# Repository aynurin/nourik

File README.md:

# NourK

ToDo:

 - [ ] Find a chip.
 - [#1](/../../issues/1) Create a layout
 - [#2](/../../issues/2) Find an existing PCB

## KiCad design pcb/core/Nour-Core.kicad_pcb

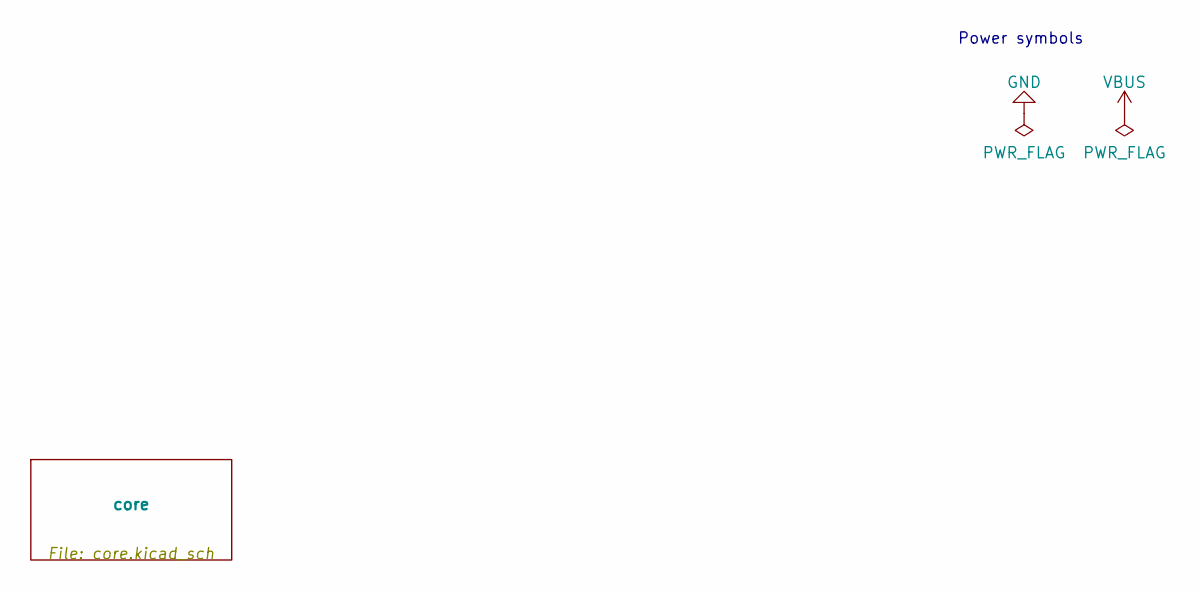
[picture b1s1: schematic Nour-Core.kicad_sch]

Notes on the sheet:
Power symbols

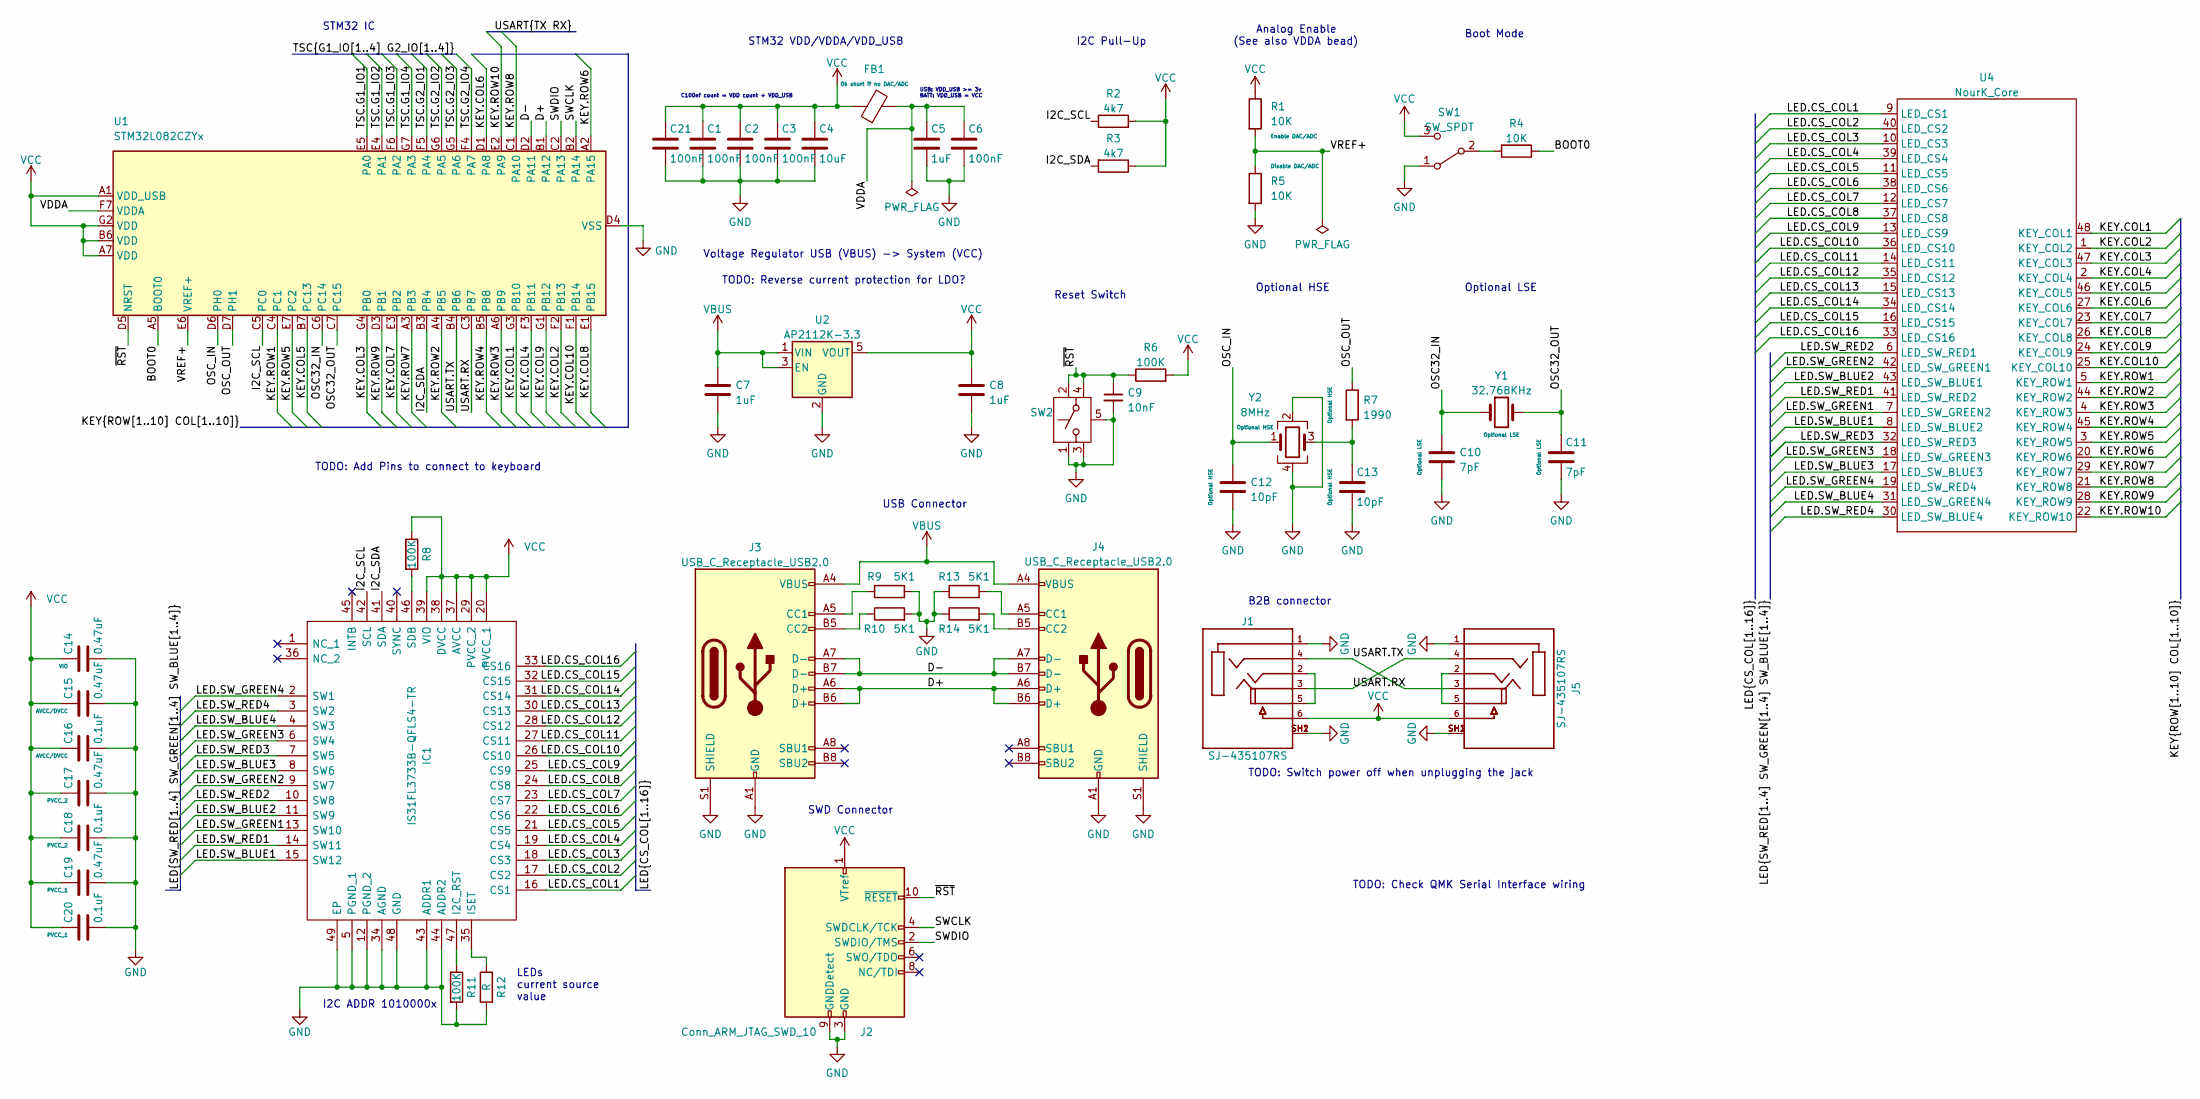
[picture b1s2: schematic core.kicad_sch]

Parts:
C1, C2, C3, C6, C21: 100nF; C_0805_2012Metric
C4: 10uF; C_0805_2012Metric
C5, C7, C8: 1uF; C_0805_2012Metric
C9: 10nF; C_0805_2012Metric
C10, C11: 7pF; C_0805_2012Metric
C12, C13: 10pF; C_0805_2012Metric
C14, C15, C17, C19: 0.47uF; C_0805_2012Metric
C16, C18, C20: 0.1uF; C_0805_2012Metric
FB1: FerriteBead; R_0805_2012Metric
IC1: IS31FL3733B-QFLS4-TR; QFN40P600X600X80-49N-D; Manufacturer_Part_Number IS31FL3733B-QFLS4-TR; Mouser Part Number 870-IS31FL3733BQFLS4
J1, J5: SJ-435107RS; CUI_SJ-435107RS
J2: Conn_ARM_JTAG_SWD_10; PinSocket_2x05_P1.27mm_Vertical
J3, J4: USB_C_Receptacle_USB2.0; GCT_USB4085-GF-A_REVA4
R1, R4, R5: 10K; R_0805_2012Metric
R2, R3: 4k7; R_0805_2012Metric
R6, R8, R11: 100K; R_0805_2012Metric
R7: 1990; R_0805_2012Metric
R9, R10, R13, R14: 5K1; R_0805_2012Metric
R12: R; R_0805_2012Metric
SW1: SW_SPDT; CSS-1211TB
SW2: SW_SPST_G; EVQP9102W; PartNo EVQ-P9102W
U1: STM32L082CZYx; ST_WLCSP-49_Die447
U2: AP2112K-3.3; SOT-23-5
U4: NourK_Core; Nour_Core
Y1: 32.768KHz; ECS327712TR; PartNo ECS-.327-7-12-TR
Y2: 8MHz; ECS801830BAGNTR; PartNo ECS-80-10-30B-CWN-TR

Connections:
/core/BOOT0: R4.1, U1.A5 (BOOT0)
/core/D+: J3.A6 (D+), J3.B6 (D+), J4.A6 (D+), J4.B6 (D+), U1.B1 (PA12)
/core/D-: J3.A7 (D-), J3.B7 (D-), J4.A7 (D-), J4.B7 (D-), U1.D2 (PA11)
/core/I2C_SCL: IC1.42 (SCL), R2.1, U1.C5 (PC0)
/core/I2C_SDA: IC1.41 (SDA), R3.2, U1.B3 (PB4)
/core/KEY.COL1: U1.G3 (PB10), U4.48 (KEY_COL1)
/core/KEY.COL2: U1.F2 (PB13), U4.1 (KEY_COL2)
/core/KEY.COL3: U1.G4 (PB0), U4.47 (KEY_COL3)
/core/KEY.COL4: U1.F3 (PB11), U4.2 (KEY_COL4)
/core/KEY.COL5: U1.B7 (PC13), U4.46 (KEY_COL5)
/core/KEY.COL6: U1.D1 (PA8), U4.27 (KEY_COL6)
/core/KEY.COL7: U1.E3 (PB2), U4.23 (KEY_COL7)
/core/KEY.COL8: U1.E1 (PB15), U4.26 (KEY_COL8)
/core/KEY.COL9: U1.G1 (PB12), U4.24 (KEY_COL9)
/core/KEY.COL10: U1.F1 (PB14), U4.25 (KEY_COL10)
/core/KEY.ROW1: U1.C4 (PC1), U4.5 (KEY_ROW1)
/core/KEY.ROW2: U1.A4 (PB5), U4.44 (KEY_ROW2)
/core/KEY.ROW3: U1.A6 (PB9), U4.4 (KEY_ROW3)
/core/KEY.ROW4: U1.B5 (PB8), U4.45 (KEY_ROW4)
/core/KEY.ROW5: U1.E7 (PC2), U4.3 (KEY_ROW5)
/core/KEY.ROW6: U1.A2 (PA15), U4.20 (KEY_ROW6)
/core/KEY.ROW7: U1.A3 (PB3), U4.29 (KEY_ROW7)
/core/KEY.ROW8: U1.C1 (PA10), U4.21 (KEY_ROW8)
/core/KEY.ROW9: U1.D3 (PB1), U4.28 (KEY_ROW9)
/core/KEY.ROW10: U1.E2 (PA9), U4.22 (KEY_ROW10)
/core/LED.CS_COL1: IC1.16 (CS1), U4.9 (LED_CS1)
/core/LED.CS_COL2: IC1.17 (CS2), U4.40 (LED_CS2)
/core/LED.CS_COL3: IC1.18 (CS3), U4.10 (LED_CS3)
/core/LED.CS_COL4: IC1.19 (CS4), U4.39 (LED_CS4)
/core/LED.CS_COL5: IC1.21 (CS5), U4.11 (LED_CS5)
/core/LED.CS_COL6: IC1.22 (CS6), U4.38 (LED_CS6)
/core/LED.CS_COL7: IC1.23 (CS7), U4.12 (LED_CS7)
/core/LED.CS_COL8: IC1.24 (CS8), U4.37 (LED_CS8)
/core/LED.CS_COL9: IC1.25 (CS9), U4.13 (LED_CS9)
/core/LED.CS_COL10: IC1.26 (CS10), U4.36 (LED_CS10)
/core/LED.CS_COL11: IC1.27 (CS11), U4.14 (LED_CS11)
/core/LED.CS_COL12: IC1.28 (CS12), U4.35 (LED_CS12)
/core/LED.CS_COL13: IC1.30 (CS13), U4.15 (LED_CS13)
/core/LED.CS_COL14: IC1.31 (CS14), U4.34 (LED_CS14)
/core/LED.CS_COL15: IC1.32 (CS15), U4.16 (LED_CS15)
/core/LED.CS_COL16: IC1.33 (CS16), U4.33 (LED_CS16)
/core/LED.SW_BLUE1: IC1.15 (SW12), U4.8 (LED_SW_BLUE2)
/core/LED.SW_BLUE2: IC1.11 (SW9), U4.43 (LED_SW_BLUE1)
/core/LED.SW_BLUE3: IC1.8 (SW6), U4.17 (LED_SW_BLUE3)
/core/LED.SW_BLUE4: IC1.4 (SW3), U4.31 (LED_SW_GREEN4)
/core/LED.SW_GREEN1: IC1.13 (SW10), U4.7 (LED_SW_GREEN2)
/core/LED.SW_GREEN2: IC1.9 (SW7), U4.42 (LED_SW_GREEN1)
/core/LED.SW_GREEN3: IC1.6 (SW4), U4.18 (LED_SW_GREEN3)
/core/LED.SW_GREEN4: IC1.2 (SW1), U4.19 (LED_SW_RED4)
/core/LED.SW_RED1: IC1.14 (SW11), U4.41 (LED_SW_RED2)
/core/LED.SW_RED2: IC1.10 (SW8), U4.6 (LED_SW_RED1)
/core/LED.SW_RED3: IC1.7 (SW5), U4.32 (LED_SW_RED3)
/core/LED.SW_RED4: IC1.3 (SW2), U4.30 (LED_SW_BLUE4)
/core/OSC32_IN: C10.1, U1.C6 (PC14), Y1.1
/core/OSC32_OUT: C11.1, U1.C7 (PC15), Y1.2
/core/OSC_IN: C12.1, U1.D6 (PH0), Y2.1
/core/OSC_OUT: R7.1, U1.D7 (PH1)
/core/SWCLK: J2.4 (SWDCLK/TCK), U1.B2 (PA14)
/core/SWDIO: J2.2 (SWDIO/TMS), U1.C2 (PA13)
/core/TSC.G1_IO1: U1.E5 (PA0)
/core/TSC.G1_IO2: U1.E4 (PA1)
/core/TSC.G1_IO3: U1.F6 (PA2)
/core/TSC.G1_IO4: U1.G7 (PA3)
/core/TSC.G2_IO1: U1.F5 (PA4)
/core/TSC.G2_IO2: U1.G6 (PA5)
/core/TSC.G2_IO3: U1.G5 (PA6)
/core/TSC.G2_IO4: U1.F4 (PA7)
/core/USART.RX: J1.3, J5.4, U1.C3 (PB7)
/core/USART.TX: J1.4, J5.3, U1.B4 (PB6)
/core/VDDA: C5.1, C6.1, FB1.2, U1.F7 (VDDA)
/core/VREF+: R1.2, R5.1, U1.E6 (VREF+)
/core/~RST: C9.1, J2.10 (~RESET), R6.1, SW2.2 (B), SW2.4 (B), U1.D5 (NRST)
GND: C1.2, C2.2, C3.2, C4.2, C5.2, C6.2, C7.2, C8.2, C9.2, C10.2, C11.2, C12.2, C13.2, C14.2, C15.2, C16.2, C17.2, C18.2, C19.2, C20.2, C21.2, IC1.5 (PGND_1), IC1.12 (PGND_2), IC1.34 (AGND), IC1.43 (ADDR1), IC1.44 (ADDR2), IC1.48 (GND), IC1.49 (EP), J1.1, J1.SH1, J1.SH2, J2.3 (GND), J2.5 (GND), J2.9 (GNDDetect), J3.A1 (GND), J3.A12 (GND), J3.B1 (GND), J3.B12 (GND), J3.S1 (SHIELD), J4.A1 (GND), J4.A12 (GND), J4.B1 (GND), J4.B12 (GND), J4.S1 (SHIELD), J5.1, J5.SH1, J5.SH2, R5.2, R9.2, R10.2, R11.2, R12.2, R13.1, R14.1, SW1.1 (A), SW2.1 (A), SW2.3 (A), SW2.5 (G), U1.D4 (VSS), U2.2 (GND), Y2.2, Y2.4
unnamed: C13.1, R7.2, Y2.3
unnamed: IC1.35 (ISET), R12.1
unnamed: IC1.46 (SDB), R8.2
unnamed: IC1.47 (I2C_RST), R11.1
unnamed: J1.2, J1.5
unnamed: J3.A5 (CC1), R9.1
unnamed: J3.B5 (CC2), R10.1
unnamed: J4.A5 (CC1), R13.2
unnamed: J4.B5 (CC2), R14.2
unnamed: J5.2, J5.5
unnamed: R4.2, SW1.2 (B)
VBUS: C7.1, J3.A4 (VBUS), J3.A9 (VBUS), J3.B4 (VBUS), J3.B9 (VBUS), J4.A4 (VBUS), J4.A9 (VBUS), J4.B4 (VBUS), J4.B9 (VBUS), U2.1 (VIN), U2.3 (EN)
VCC: C1.1, C2.1, C3.1, C4.1, C8.1, C14.1, C15.1, C16.1, C17.1, C18.1, C19.1, C20.1, C21.1, FB1.1, IC1.20 (PVCC_1), IC1.29 (PVCC_2), IC1.37 (AVCC), IC1.38 (DVCC), IC1.39 (VIO), J1.6, J2.1 (VTref), J5.6, R1.1, R2.2, R3.1, R6.2, R8.1, SW1.3 (C), U1.A1 (VDD_USB), U1.A7 (VDD), U1.B6 (VDD), U1.G2 (VDD), U2.5 (VOUT)

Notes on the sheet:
Boot Mode
Voltage Regulator USB (VBUS) -> System (VCC)
C100nf count = VDD count + VDD_USB
STM32 VDD/VDDA/VDD_USB
I2C Pull-Up
Optional LSE
LEDs current source value
TODO: Switch power off when unplugging the jack
I2C ADDR 1010000x
Optional HSE
Reset Switch
STM32 IC
TODO: Check QMK Serial Interface wiring
Analog Enable (See also VDDA bead)
SWD Connector
TODO: Reverse current protection for LDO?
USB Connector
TODO: Add Pins to connect to keyboard
B2B connector
USB: VDD_USB >= 3v BATT: VDD_USB = VCC

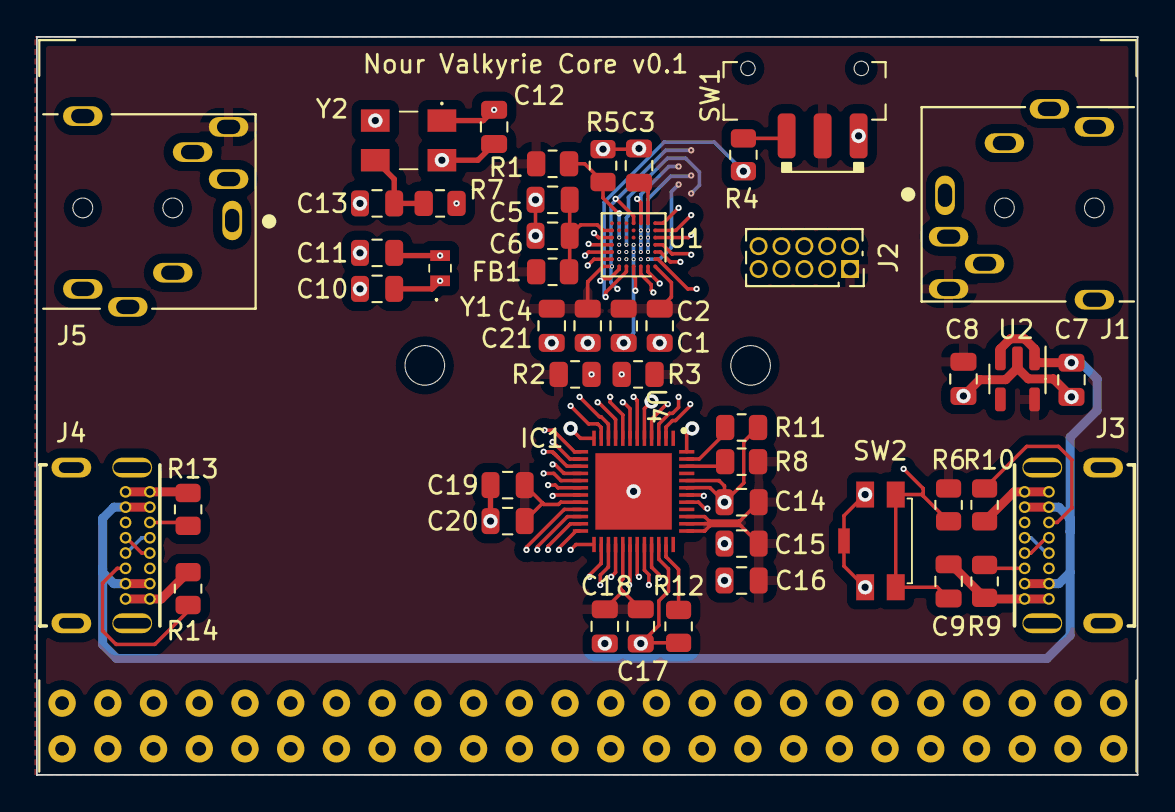
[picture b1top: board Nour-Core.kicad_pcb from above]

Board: 4 copper layers, 61.2 x 41.0 mm, 49 parts (0 on the bottom side), 78 nets.

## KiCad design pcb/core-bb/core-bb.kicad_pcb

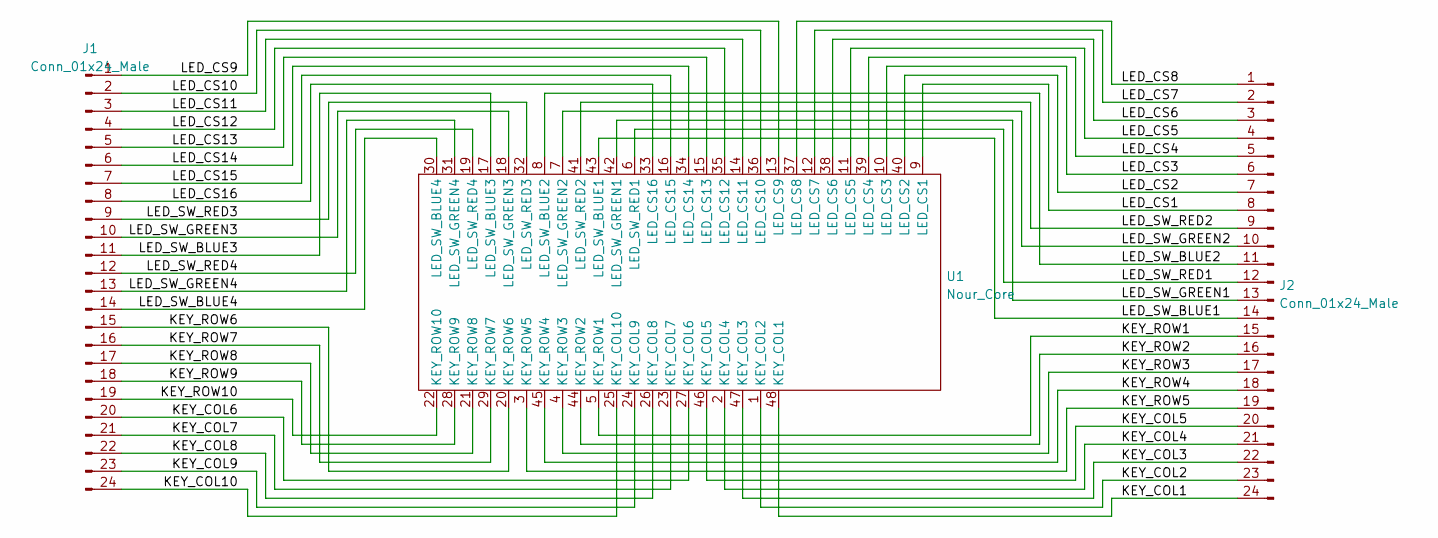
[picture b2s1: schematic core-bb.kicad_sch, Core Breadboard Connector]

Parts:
J1, J2: Conn_01x24_Male; PinHeader_1x24_P2.54mm_Vertical
U1: Nour_Core

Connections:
/KEY_COL1: J2.24, U1.48 (KEY_COL1)
/KEY_COL2: J2.23, U1.1 (KEY_COL2)
/KEY_COL3: J2.22, U1.47 (KEY_COL3)
/KEY_COL4: J2.21, U1.2 (KEY_COL4)
/KEY_COL5: J2.20, U1.46 (KEY_COL5)
/KEY_COL6: J1.20, U1.27 (KEY_COL6)
/KEY_COL7: J1.21, U1.23 (KEY_COL7)
/KEY_COL8: J1.22, U1.26 (KEY_COL8)
/KEY_COL9: J1.23, U1.24 (KEY_COL9)
/KEY_COL10: J1.24, U1.25 (KEY_COL10)
/KEY_ROW1: J2.15, U1.5 (KEY_ROW1)
/KEY_ROW2: J2.16, U1.44 (KEY_ROW2)
/KEY_ROW3: J2.17, U1.4 (KEY_ROW3)
/KEY_ROW4: J2.18, U1.45 (KEY_ROW4)
/KEY_ROW5: J2.19, U1.3 (KEY_ROW5)
/KEY_ROW6: J1.15, U1.20 (KEY_ROW6)
/KEY_ROW7: J1.16, U1.29 (KEY_ROW7)
/KEY_ROW8: J1.17, U1.21 (KEY_ROW8)
/KEY_ROW9: J1.18, U1.28 (KEY_ROW9)
/KEY_ROW10: J1.19, U1.22 (KEY_ROW10)
/LED_CS1: J2.8, U1.9 (LED_CS1)
/LED_CS2: J2.7, U1.40 (LED_CS2)
/LED_CS3: J2.6, U1.10 (LED_CS3)
/LED_CS4: J2.5, U1.39 (LED_CS4)
/LED_CS5: J2.4, U1.11 (LED_CS5)
/LED_CS6: J2.3, U1.38 (LED_CS6)
/LED_CS7: J2.2, U1.12 (LED_CS7)
/LED_CS8: J2.1, U1.37 (LED_CS8)
/LED_CS9: J1.1, U1.13 (LED_CS9)
/LED_CS10: J1.2, U1.36 (LED_CS10)
/LED_CS11: J1.3, U1.14 (LED_CS11)
/LED_CS12: J1.4, U1.35 (LED_CS12)
/LED_CS13: J1.5, U1.15 (LED_CS13)
/LED_CS14: J1.6, U1.34 (LED_CS14)
/LED_CS15: J1.7, U1.16 (LED_CS15)
/LED_CS16: J1.8, U1.33 (LED_CS16)
/LED_SW_BLUE1: J2.14, U1.43 (LED_SW_BLUE1)
/LED_SW_BLUE2: J2.11, U1.8 (LED_SW_BLUE2)
/LED_SW_BLUE3: J1.11, U1.17 (LED_SW_BLUE3)
/LED_SW_BLUE4: J1.14, U1.30 (LED_SW_BLUE4)
/LED_SW_GREEN1: J2.13, U1.42 (LED_SW_GREEN1)
/LED_SW_GREEN2: J2.10, U1.7 (LED_SW_GREEN2)
/LED_SW_GREEN3: J1.10, U1.18 (LED_SW_GREEN3)
/LED_SW_GREEN4: J1.13, U1.31 (LED_SW_GREEN4)
/LED_SW_RED1: J2.12, U1.6 (LED_SW_RED1)
/LED_SW_RED2: J2.9, U1.41 (LED_SW_RED2)
/LED_SW_RED3: J1.9, U1.32 (LED_SW_RED3)
/LED_SW_RED4: J1.12, U1.19 (LED_SW_RED4)

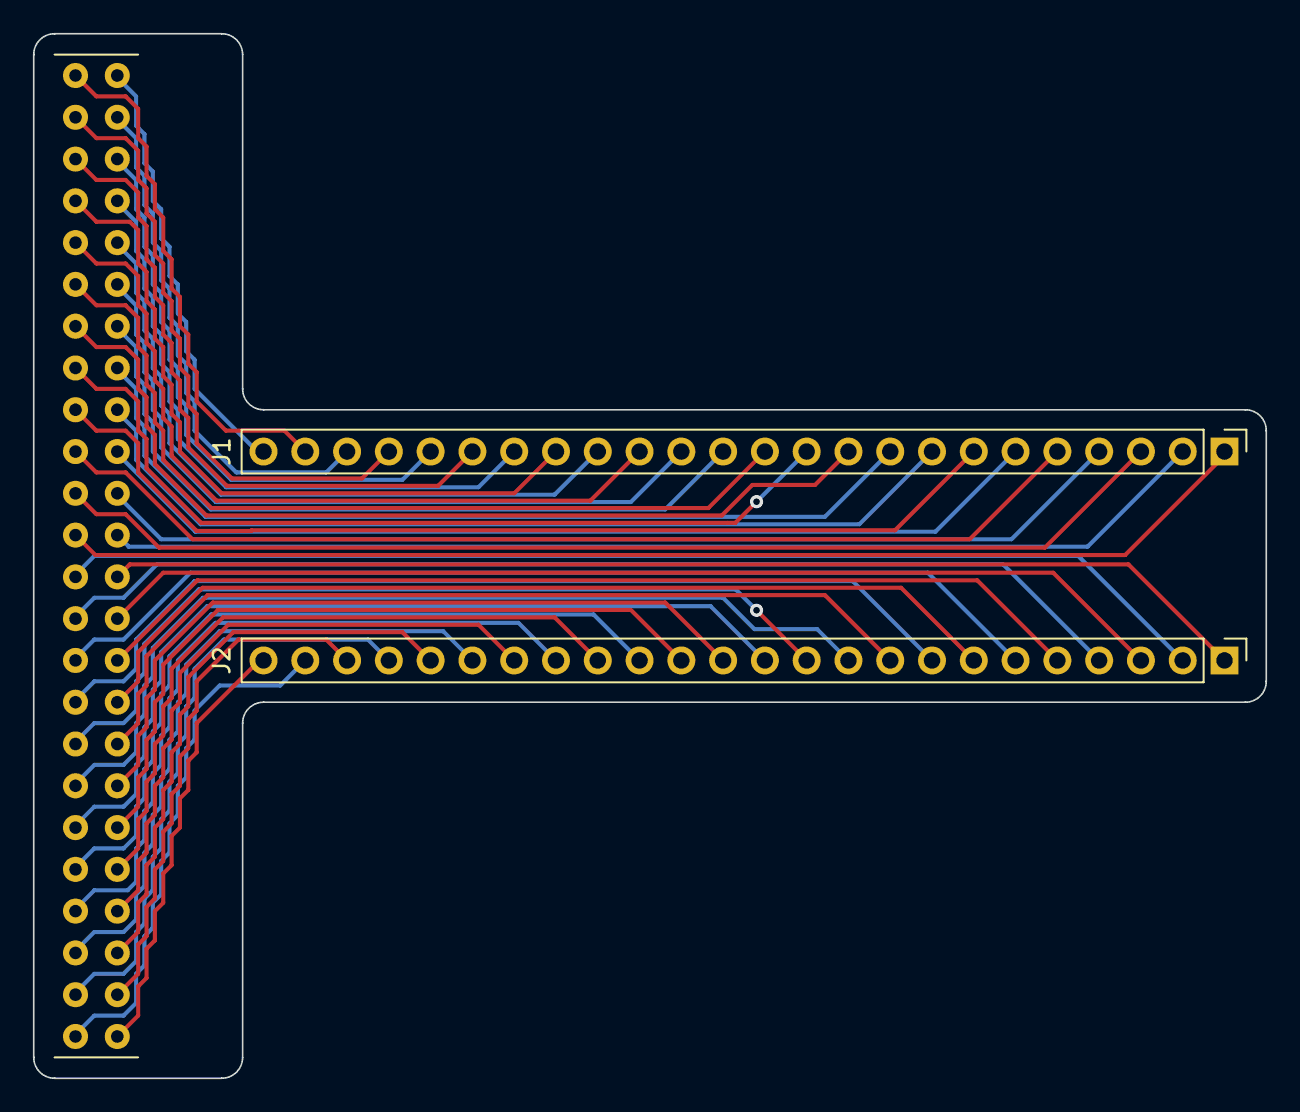
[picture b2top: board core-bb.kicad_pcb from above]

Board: 2 copper layers, 74.9 x 63.5 mm, 3 parts (0 on the bottom side), 48 nets.

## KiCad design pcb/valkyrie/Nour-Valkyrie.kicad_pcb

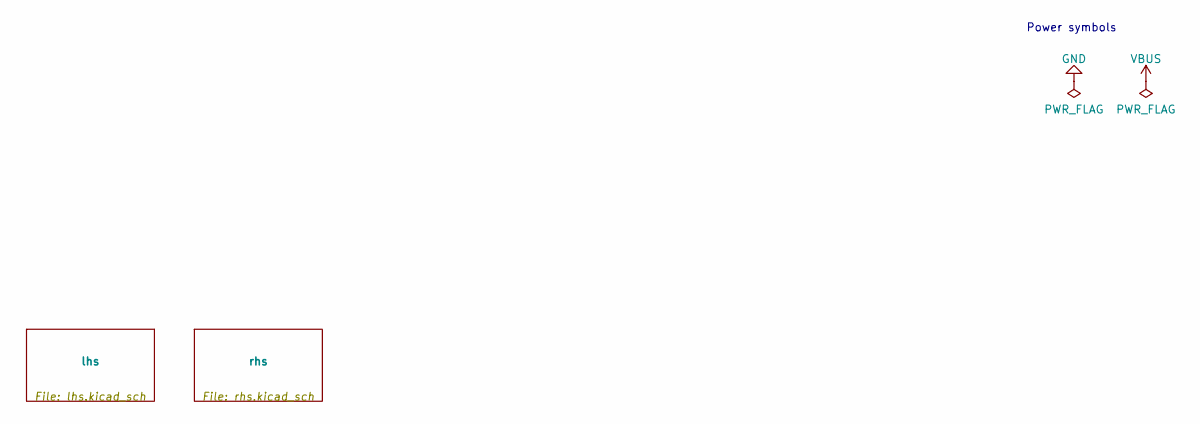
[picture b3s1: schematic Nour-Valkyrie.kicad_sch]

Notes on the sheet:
Power symbols

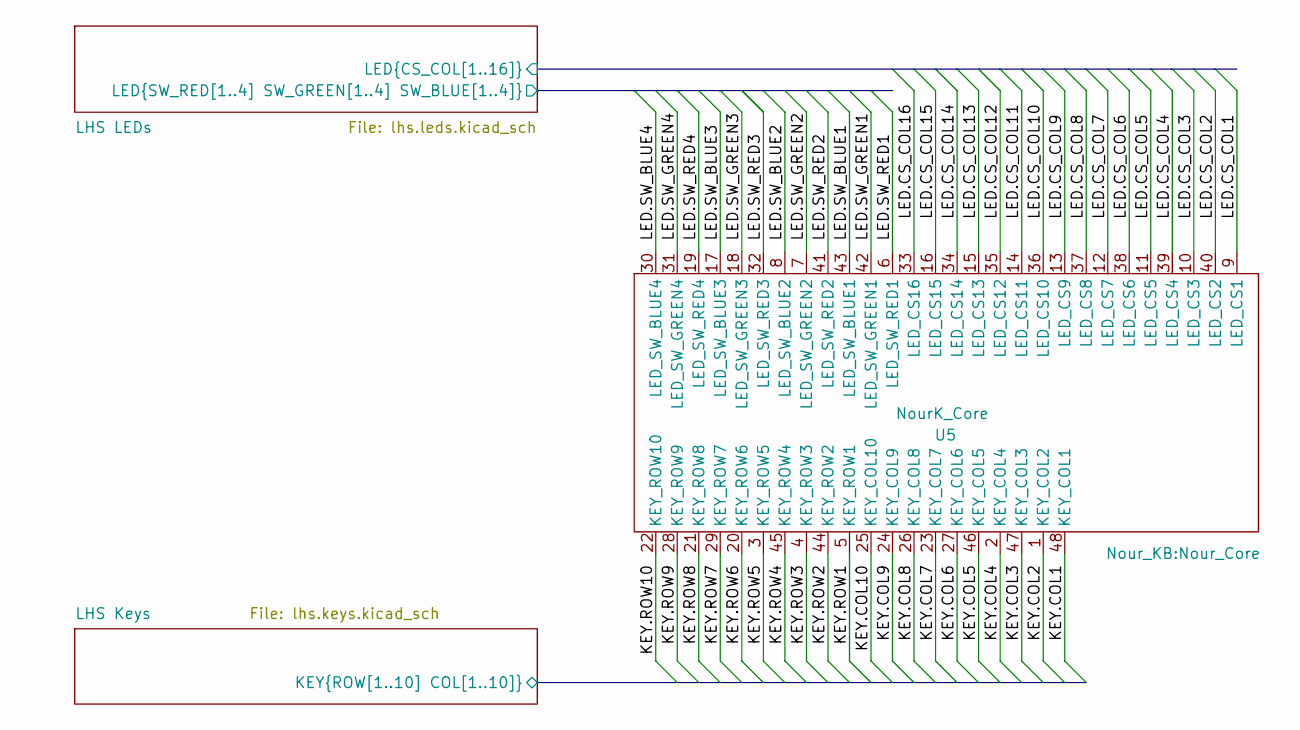
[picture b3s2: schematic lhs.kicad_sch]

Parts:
U5: NourK_Core; Nour_Core

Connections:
/lhs/LHS Keys/KEY.COL1: U5.48 (KEY_COL1); also elsewhere on the board
/lhs/LHS Keys/KEY.COL2: U5.1 (KEY_COL2); also elsewhere on the board
/lhs/LHS Keys/KEY.COL3: U5.47 (KEY_COL3); also elsewhere on the board
/lhs/LHS Keys/KEY.COL4: U5.2 (KEY_COL4); also elsewhere on the board
/lhs/LHS Keys/KEY.COL5: U5.46 (KEY_COL5); also elsewhere on the board
/lhs/LHS Keys/KEY.COL6: U5.27 (KEY_COL6); also elsewhere on the board
/lhs/LHS Keys/KEY.COL7: U5.23 (KEY_COL7); also elsewhere on the board
/lhs/LHS Keys/KEY.COL8: U5.26 (KEY_COL8)
/lhs/LHS Keys/KEY.COL9: U5.24 (KEY_COL9)
/lhs/LHS Keys/KEY.COL10: U5.25 (KEY_COL10)
/lhs/LHS Keys/KEY.ROW1: U5.5 (KEY_ROW1); also elsewhere on the board
/lhs/LHS Keys/KEY.ROW2: U5.44 (KEY_ROW2); also elsewhere on the board
/lhs/LHS Keys/KEY.ROW3: U5.4 (KEY_ROW3)
/lhs/LHS Keys/KEY.ROW4: U5.45 (KEY_ROW4)
/lhs/LHS Keys/KEY.ROW5: U5.3 (KEY_ROW5)
/lhs/LHS Keys/KEY.ROW6: U5.20 (KEY_ROW6)
/lhs/LHS Keys/KEY.ROW7: U5.29 (KEY_ROW7)
/lhs/LHS Keys/KEY.ROW8: U5.21 (KEY_ROW8)
/lhs/LHS Keys/KEY.ROW9: U5.28 (KEY_ROW9); also elsewhere on the board
/lhs/LHS Keys/KEY.ROW10: U5.22 (KEY_ROW10); also elsewhere on the board
/lhs/LHS LEDs/LED.CS_COL1: U5.9 (LED_CS1); also elsewhere on the board
/lhs/LHS LEDs/LED.CS_COL2: U5.40 (LED_CS2); also elsewhere on the board
/lhs/LHS LEDs/LED.CS_COL3: U5.10 (LED_CS3); also elsewhere on the board
/lhs/LHS LEDs/LED.CS_COL4: U5.39 (LED_CS4); also elsewhere on the board
/lhs/LHS LEDs/LED.CS_COL5: U5.11 (LED_CS5); also elsewhere on the board
/lhs/LHS LEDs/LED.CS_COL6: U5.38 (LED_CS6); also elsewhere on the board
/lhs/LHS LEDs/LED.CS_COL7: U5.12 (LED_CS7); also elsewhere on the board
/lhs/LHS LEDs/LED.CS_COL8: U5.37 (LED_CS8); also elsewhere on the board
/lhs/LHS LEDs/LED.CS_COL9: U5.13 (LED_CS9); also elsewhere on the board
/lhs/LHS LEDs/LED.CS_COL10: U5.36 (LED_CS10); also elsewhere on the board
/lhs/LHS LEDs/LED.CS_COL11: U5.14 (LED_CS11); also elsewhere on the board
/lhs/LHS LEDs/LED.CS_COL12: U5.35 (LED_CS12)
/lhs/LHS LEDs/LED.CS_COL13: U5.15 (LED_CS13)
/lhs/LHS LEDs/LED.CS_COL14: U5.34 (LED_CS14)
/lhs/LHS LEDs/LED.CS_COL15: U5.16 (LED_CS15)
/lhs/LHS LEDs/LED.CS_COL16: U5.33 (LED_CS16)
/lhs/LHS LEDs/LED.SW_BLUE1: U5.43 (LED_SW_BLUE1); also elsewhere on the board
/lhs/LHS LEDs/LED.SW_BLUE2: U5.8 (LED_SW_BLUE2); also elsewhere on the board
/lhs/LHS LEDs/LED.SW_BLUE3: U5.17 (LED_SW_BLUE3); also elsewhere on the board
/lhs/LHS LEDs/LED.SW_BLUE4: U5.30 (LED_SW_BLUE4); also elsewhere on the board
/lhs/LHS LEDs/LED.SW_GREEN1: U5.42 (LED_SW_GREEN1); also elsewhere on the board
/lhs/LHS LEDs/LED.SW_GREEN2: U5.7 (LED_SW_GREEN2); also elsewhere on the board
/lhs/LHS LEDs/LED.SW_GREEN3: U5.18 (LED_SW_GREEN3); also elsewhere on the board
/lhs/LHS LEDs/LED.SW_GREEN4: U5.31 (LED_SW_GREEN4); also elsewhere on the board
/lhs/LHS LEDs/LED.SW_RED1: U5.6 (LED_SW_RED1); also elsewhere on the board
/lhs/LHS LEDs/LED.SW_RED2: U5.41 (LED_SW_RED2); also elsewhere on the board
/lhs/LHS LEDs/LED.SW_RED3: U5.32 (LED_SW_RED3); also elsewhere on the board
/lhs/LHS LEDs/LED.SW_RED4: U5.19 (LED_SW_RED4); also elsewhere on the board

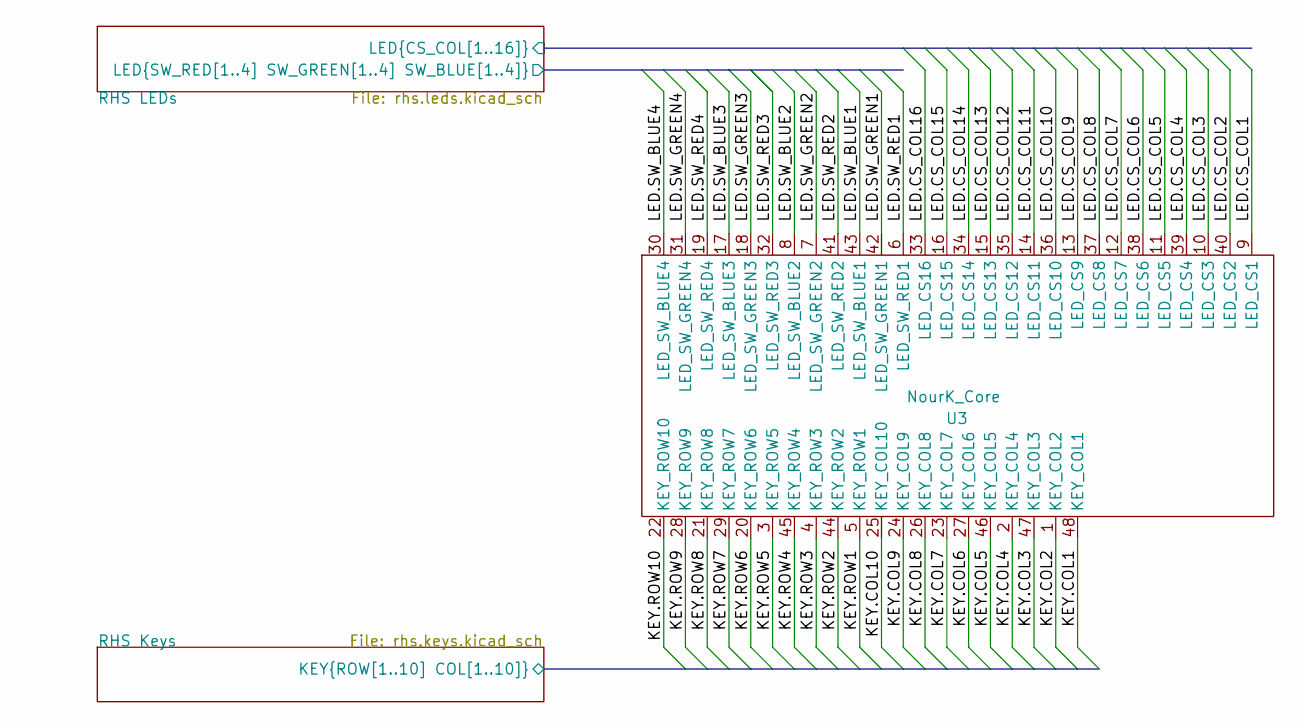
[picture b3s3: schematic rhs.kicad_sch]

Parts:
U3: NourK_Core; Nour_Core

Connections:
/rhs/RHS Keys/KEY.COL1: U3.48 (KEY_COL1); also elsewhere on the board
/rhs/RHS Keys/KEY.COL2: U3.1 (KEY_COL2); also elsewhere on the board
/rhs/RHS Keys/KEY.COL3: U3.47 (KEY_COL3)
/rhs/RHS Keys/KEY.COL4: U3.2 (KEY_COL4)
/rhs/RHS Keys/KEY.COL5: U3.46 (KEY_COL5)
/rhs/RHS Keys/KEY.COL6: U3.27 (KEY_COL6); also elsewhere on the board
/rhs/RHS Keys/KEY.COL7: U3.23 (KEY_COL7); also elsewhere on the board
/rhs/RHS Keys/KEY.COL8: U3.26 (KEY_COL8); also elsewhere on the board
/rhs/RHS Keys/KEY.COL9: U3.24 (KEY_COL9); also elsewhere on the board
/rhs/RHS Keys/KEY.COL10: U3.25 (KEY_COL10); also elsewhere on the board
/rhs/RHS Keys/KEY.ROW1: U3.5 (KEY_ROW1)
/rhs/RHS Keys/KEY.ROW2: U3.44 (KEY_ROW2)
/rhs/RHS Keys/KEY.ROW3: U3.4 (KEY_ROW3); also elsewhere on the board
/rhs/RHS Keys/KEY.ROW4: U3.45 (KEY_ROW4); also elsewhere on the board
/rhs/RHS Keys/KEY.ROW5: U3.3 (KEY_ROW5)
/rhs/RHS Keys/KEY.ROW6: U3.20 (KEY_ROW6)
/rhs/RHS Keys/KEY.ROW7: U3.29 (KEY_ROW7)
/rhs/RHS Keys/KEY.ROW8: U3.21 (KEY_ROW8); also elsewhere on the board
/rhs/RHS Keys/KEY.ROW9: U3.28 (KEY_ROW9); also elsewhere on the board
/rhs/RHS Keys/KEY.ROW10: U3.22 (KEY_ROW10)
/rhs/RHS LEDs/LED.CS_COL1: U3.9 (LED_CS1)
/rhs/RHS LEDs/LED.CS_COL2: U3.40 (LED_CS2)
/rhs/RHS LEDs/LED.CS_COL3: U3.10 (LED_CS3)
/rhs/RHS LEDs/LED.CS_COL4: U3.39 (LED_CS4)
/rhs/RHS LEDs/LED.CS_COL5: U3.11 (LED_CS5)
/rhs/RHS LEDs/LED.CS_COL6: U3.38 (LED_CS6); also elsewhere on the board
/rhs/RHS LEDs/LED.CS_COL7: U3.12 (LED_CS7); also elsewhere on the board
/rhs/RHS LEDs/LED.CS_COL8: U3.37 (LED_CS8); also elsewhere on the board
/rhs/RHS LEDs/LED.CS_COL9: U3.13 (LED_CS9); also elsewhere on the board
/rhs/RHS LEDs/LED.CS_COL10: U3.36 (LED_CS10); also elsewhere on the board
/rhs/RHS LEDs/LED.CS_COL11: U3.14 (LED_CS11); also elsewhere on the board
/rhs/RHS LEDs/LED.CS_COL12: U3.35 (LED_CS12); also elsewhere on the board
/rhs/RHS LEDs/LED.CS_COL13: U3.15 (LED_CS13); also elsewhere on the board
/rhs/RHS LEDs/LED.CS_COL14: U3.34 (LED_CS14); also elsewhere on the board
/rhs/RHS LEDs/LED.CS_COL15: U3.16 (LED_CS15); also elsewhere on the board
/rhs/RHS LEDs/LED.CS_COL16: U3.33 (LED_CS16); also elsewhere on the board
/rhs/RHS LEDs/LED.SW_BLUE1: U3.43 (LED_SW_BLUE1); also elsewhere on the board
/rhs/RHS LEDs/LED.SW_BLUE2: U3.8 (LED_SW_BLUE2); also elsewhere on the board
/rhs/RHS LEDs/LED.SW_BLUE3: U3.17 (LED_SW_BLUE3); also elsewhere on the board
/rhs/RHS LEDs/LED.SW_BLUE4: U3.30 (LED_SW_BLUE4); also elsewhere on the board
/rhs/RHS LEDs/LED.SW_GREEN1: U3.42 (LED_SW_GREEN1); also elsewhere on the board
/rhs/RHS LEDs/LED.SW_GREEN2: U3.7 (LED_SW_GREEN2); also elsewhere on the board
/rhs/RHS LEDs/LED.SW_GREEN3: U3.18 (LED_SW_GREEN3); also elsewhere on the board
/rhs/RHS LEDs/LED.SW_GREEN4: U3.31 (LED_SW_GREEN4); also elsewhere on the board
/rhs/RHS LEDs/LED.SW_RED1: U3.6 (LED_SW_RED1); also elsewhere on the board
/rhs/RHS LEDs/LED.SW_RED2: U3.41 (LED_SW_RED2); also elsewhere on the board
/rhs/RHS LEDs/LED.SW_RED3: U3.32 (LED_SW_RED3); also elsewhere on the board
/rhs/RHS LEDs/LED.SW_RED4: U3.19 (LED_SW_RED4); also elsewhere on the board
